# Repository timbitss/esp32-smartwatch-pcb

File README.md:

# ESP32 Smartwatch PCB

## Blinky Test

## Schematic

## All Layers

## Top Layer: Signal

## Inner Layer 1: GND

## Inner Layer 2: VCC + Signal

## Bottom Layer: Signal

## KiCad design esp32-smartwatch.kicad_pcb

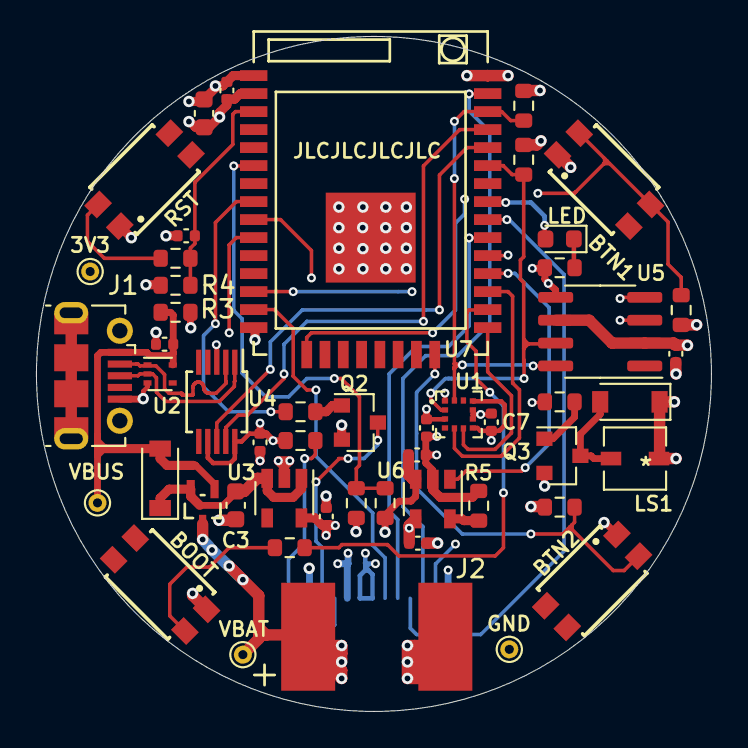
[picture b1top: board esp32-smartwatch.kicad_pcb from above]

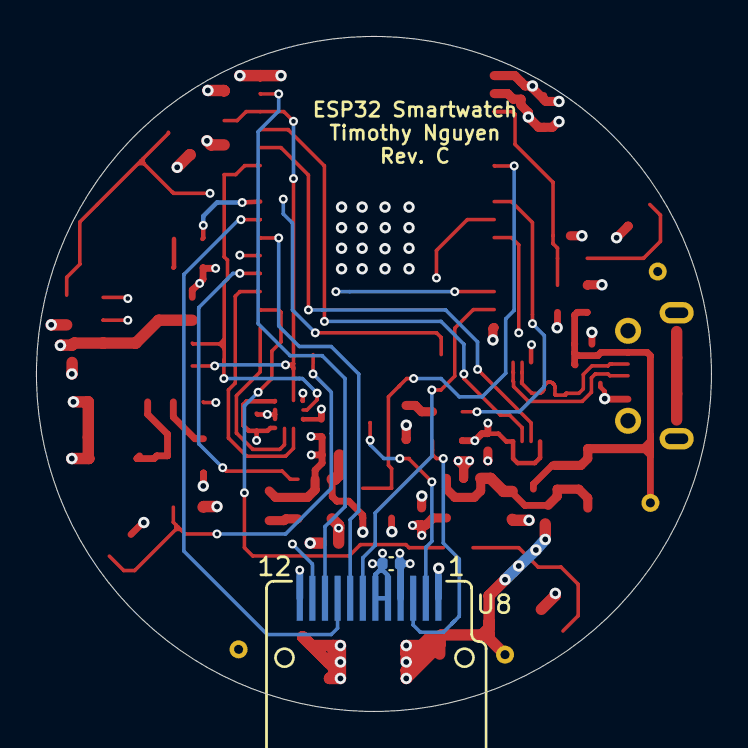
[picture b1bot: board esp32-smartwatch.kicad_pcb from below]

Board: 4 copper layers, 37.5 x 37.5 mm, 53 parts (2 on the bottom side), 38 nets.

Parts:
3V3: +3V3; TestPoint_THTPad_D1.0mm_Drill0.5mm
BOOT: SW1; switch
BTN1: SW3; switch
BTN2: SW4; switch
C1, C2, C4, C6, C7, C9, C10, C13: 0.1uF; C_0402_1005Metric
C3, C8: 10uF; C_0603_1608Metric
C5, C11, C12: 4.7uF; C_0402_1005Metric
D1, D3: MBR120LSF; D_SOD-123
GND: GND; TestPoint_THTPad_D1.0mm_Drill0.5mm
J1: USB_B_Micro; USB_Micro-B_Molex-105017-0001
J2: LiPo_JST; Custom_pad
LED: STATUS; LED_0603_1608Metric
LS1: ‎SMT-0340-T-R‎; SMT-0340-T-R
Q1: SI1317DL-T1-GE3; SOT65P210X110-3N
Q2, Q3: BSS123; SOT-23
R1, R2, R5: 4.7K; R_0603_1608Metric
R3, R7, R8: 100K; R_0603_1608Metric
R4, R14, R16: 10K; R_0603_1608Metric
R9, R11, R13: 330; R_0603_1608Metric
R10, R12: 150; R_0603_1608Metric
R15: 22; R_0603_1608Metric
RST: SW2; switch
U1: BMA423; IC_BMA400
U2: TPD3E001DRLR; SOT-553
U3: XC6220B331MR; SOT-23-5
U4: CH340E; MSOP-10_3x3mm_P0.5mm
U5: DS3231MZ; SOIC-8_3.9x4.9mm_P1.27mm
U6: MCP73831-2-OT; SOT-23-5
U7: ttgo-32-micro
U8: GC9A01_IPS_display_SPI; GC9A01_IPS_display_under
VBAT: VBAT; TestPoint_THTPad_D1.0mm_Drill0.5mm
VBUS: VBUS; TestPoint_THTPad_D1.0mm_Drill0.5mm

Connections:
+3V3: 3V3.1, C1.2, C4.1, C5.1, C6.2, C7.1, C8.1, C9.1, C13.1, D3.1, LS1.1, R1.1, R2.1, R4.1, R14.1, R15.1, R16.1, U1.3, U1.7, U1.10, U3.5, U4.7, U4.10, U5.2, U5.6, U7.2, U8.4
/ALARM: R12.1, U7.9
/BAT_LVL: R7.2, R8.1, U7.6
/BAT_STAT: U6.1, U7.27
/BMA_INT1: U1.5, U7.26
/BMA_INT2: U1.6, U7.24
/BOOT: R11.2, U7.25
/BTN1: BTN1.2, BTN1.4, R14.2, U7.16
/BTN2: BTN2.2, R16.2, U7.23
/D+: J1.3, U2.2, U4.1
/D-: J1.2, U2.1, U4.2
/IO19: LED.2, U7.31
/LEDK: R10.1, U7.8
/MOSI: U7.37, U8.10
/RXD0: U4.8, U7.34
/SCL: R2.2, U1.12, U5.8, U7.36
/SCLK: U7.30, U8.9
/SDA: R1.2, U1.2, U5.7, U7.33
/TFT_DC: U7.14, U8.7
/TXD0: U4.9, U7.35
/~DS_INT: U5.3, U7.13
/~DS_RST: U5.4, U7.28
/~RST: C10.1, R4.2, R13.2, U7.3
/~TFT_CS: U7.29, U8.8
/~TFT_RST: U7.10, U8.11
GND: BOOT.1, BTN1.1, BTN2.1, C1.1, C2.2, C3.2, C4.2, C5.2, C6.1, C7.2, C8.2, C9.2, C10.2, C11.2, C12.2, C13.2, GND.1, J1.5, J2.2, Q2.2, Q3.2, R3.2, R5.2, R8.2, R9.2, RST.1, U1.1, U1.8, U1.9, U2.3, U3.2, U4.3, U5.5, U6.2, U7.1, U7.15, U7.38, U7.EP, U8.1, U8.5, U8.6, U8.12
unnamed: BOOT.2, R11.1
unnamed: C3.1, D1.1, Q1.2, U3.1, U3.3
unnamed: LED.1, R9.1
unnamed: D3.2, LS1.2, Q3.3
unnamed: Q2.1, R10.2
unnamed: Q2.3, U8.2
unnamed: Q3.1, R12.2
unnamed: R5.1, U6.5
unnamed: R13.1, RST.2
unnamed: R15.2, U8.3
VBAT: C12.1, J2.1, Q1.3, R7.1, U6.3, VBAT.1
VBUS: C2.1, C11.1, D1.2, J1.1, Q1.1, R3.1, U2.5, U6.4, VBUS.1

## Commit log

2021-06-26 Added KiCAD files
2021-06-26 Untracked files in .gitignore
2021-06-26 Removed cached files
2021-08-05 updated images
2021-08-05 Added images to README
2021-08-05 updating README
2021-08-14 Redoing PCB
2021-08-14 Revising PCB
2021-08-14 Revised schematic
2021-08-16 PCB layout Rev C
2021-09-07 Added blinky gif

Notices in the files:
parts and their libraries:
Copyright 2021 Accelerated Designs. All rights reserved.
